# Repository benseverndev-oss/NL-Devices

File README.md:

# NL-Devices

Natural-language → **validated** electronic schematic/netlist + BOM, eventually a
routed PCB exportable to fab (PCBWay/JLCPCB).

An LLM orchestrator composes **pre-verified subcircuit blocks** (not synthesis from
scratch), validated against a ground-truth component database, with deterministic
compile-to-netlist and verification. The product is *correctness*; natural language
is the interface.

## Docs

- **[DESIGN.md](./DESIGN.md)** — product thesis, target architecture, and the
  adopt/build/avoid decisions.
- **[BUSINESS.md](./BUSINESS.md)** — monetization & business-model strategy
  (the layered, sequenced revenue model).
- **[SPIKE.md](./SPIKE.md)** — Phase-0 engineering spike: verified blocks +
  seam validation, and the atopile-vs-SKiDL bake-off. *(Steps 0–6 complete — see
  `spike/`.)*
- **[DECISION.md](./DECISION.md)** — spike decision memo: scorecard + chosen
  substrate/architecture (atopile + custom seam-validator + ngspice harness).
- **[ORCHESTRATOR.md](./ORCHESTRATOR.md)** — NL → validated-design orchestrator
  prototype: composes verified blocks, gated by the seam-validator.
- **[RESEARCH.md](./RESEARCH.md)** — cited prior-art & competitive research with
  confidence levels behind every decision.
- **[GAPS.md](./GAPS.md)** — gap audit: honest distance from the running spike to the
  ultimate goal (verified by executing every component), with prioritized next steps.
- **[SPEC-NL-PLANNER.md](./SPEC-NL-PLANNER.md)** — implementation spec for the top
  gap: wiring a real Claude planner into the existing validator-gated seam, with an
  eval harness and CI.
- **[SPEC-PARTDB.md](./SPEC-PARTDB.md)** — implementation spec for the ground-truth
  part-data layer: a sourced, pinned component snapshot + an offline CI gate that
  catches a wrong LCSC code / MPN / footprint / supply voltage in a block's YAML
  (closes the GAPS §4d 🔴).
- **[SPEC-VALIDATOR-DEPTH.md](./SPEC-VALIDATOR-DEPTH.md)** — deepening the validator
  (3→9 checks, incl. `part-rail-rating` joining it to the part DB, plus
  `power-connectivity` + `i2c-multimaster`) and an adversarial corpus that **measures
  the false-negative rate** (walked 33% → 22% → 0% over the representable known-bad
  designs), with the remaining `NOT_MODELLED` gaps named as the roadmap (GAPS §4c).
- **[SPEC-SPICE.md](./SPEC-SPICE.md)** — replacing the "Ohm's-law-in-a-SPICE-costume"
  electrical gate with an honest analytic dropout check + **genuine ngspice `.tran`
  sims** (I2C rise time, rail droop) that cross-check the analytic limit (GAPS §3/§5.6).
- **[SPEC-FAB-EXPORT.md](./SPEC-FAB-EXPORT.md)** — spiking one fab path: a JLCPCB
  package (real-LCSC BOM + CPL + format-valid Gerber/drill) and a validated **dry-run**
  order, honest that copper routing is still the upstream blocker (GAPS §4e/§5.7).
- **[SPEC-ROUTING.md](./SPEC-ROUTING.md)** — owning the autoroute: a CI-gated pipeline
  (`place.py` + headless **freerouting** + `kicad-cli`) that turns the `ato build` board
  into **routed, DRC-clean copper Gerbers**, folded back into the fab package. Closes the
  GAPS §4e routing 🔴 and reverses the DESIGN §4 autoroute decision (AVOID → qualified BUILD).

> Status: early scoping / pre-build.

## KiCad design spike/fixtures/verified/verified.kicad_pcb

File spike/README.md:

# Spike Log

Progress against the [`SPIKE.md`](../SPIKE.md) plan. Step 0 = toolchain baseline;
Step 1 = the 3-block typed slice in atopile.

---

# Step 0: Toolchain Baseline (COMPLETE ✅)

Green baseline for the [`SPIKE.md`](../SPIKE.md) bake-off. Establishes that both
substrates and the SPICE-validation leg run end-to-end on a trivial circuit, and
records the environment decisions for the real slice (steps 1–6).

## Result — all three legs green

| Leg | Hello-world | Status | Proven capability |
|---|---|---|---|
| **atopile** | `atopile/` divider → `ato build` | ✅ | Compiles, **constraint solver** runs (post-design/post-solve checks), **JLCPCB part-picker resolves real parts**, emits netlist + BOM + `.kicad_pcb` |
| **SKiDL** | `skidl/hello_skidl.py` | ✅ | Builds circuit, **`ERC()` runs** (correctly flagged the open-ended divider nets), emits a KiCad netlist |
| **SPICE** | `skidl/ngspice_check.py` | ✅ | DC operating point via a **BSD-clean ngspice wrapper** (`V(MID)=2.500V`) |

Evidence — atopile picked a real part for the 10 kΩ 0402:
```
Designator,Footprint,Quantity,Value,Manufacturer,Partnumber,LCSC Part #
"R1, R2",R0402,2,10kΩ ±1% 62.5mW,UNI-ROYAL(Uniroyal Elec),0402WGF1002TCE,C25744
```

## Key findings (feed the bake-off + de-risk later steps)

1. **PySpice is dead for our purposes — confirmed empirically.** PySpice 1.5 (the
   last PyPI release, 2021; GitHub "git" is also 1.5) is **incompatible with ngspice
   42**: the shared-lib path errors `Unsupported Ngspice version 42 / Command 'run'
   failed`, and the subprocess path errors `Expected label Circuit instead of Note`
   (its raw parser chokes on ngspice 42's new header). This is exactly the
   maintenance risk flagged in [`RESEARCH.md`](../RESEARCH.md) §4c.
   → **Decision: drive the `ngspice` binary directly** (`ngspice_check.py`).
   ngspice is **BSD** (safe to embed) vs. PySpice's **GPLv3** — so this also keeps
   the SPICE leg out of our proprietary core, as DESIGN.md intended. SKiDL's own
   `skidl.pyspice` mode is therefore unavailable; not needed.

2. **atopile *does* emit a standalone netlist** (`build/builds/divider/divider/divider.net`)
   alongside `.kicad_pcb`, `divider.bom.csv`, and `*.variables.md` / `*.i2c_tree.md`
   reports. → Resolves the open question in SPIKE.md §8.

3. **atopile part-picking needs network** (hits the JLCPCB/LCSC parts DB; ~5 s for
   2 passives). Works under this environment's network policy. Plan for offline/CI.

4. **Substrate API specifics learned** (for writing the real blocks):
   - atopile `Resistor` exposes `unnamed[0]` / `unnamed[1]` (faebryk); `Electrical`
     and `Resistor` must each be `import`ed. Values are native: `10kohm +/- 5%`.
   - SKiDL needs KiCad symbol libs; we use the **monolithic** format (KiCad tag
     `8.0.0`), not GitLab master's new split `*.kicad_symdir/` layout.

5. **Version note:** atopile is **pinned to 0.12.5 on Python 3.13** (latest is 0.15.7,
   but 0.13+ needs Python 3.14, which is RC and crashed the CLI). The pin lives in
   `../scripts/setup.sh` / `setup.ps1`, `../.python-version`, and `atopile/ato.yaml`
   (`>=0.12.5`); `../scripts/check_toolchain.py` keeps them in sync. Upgrade
   deliberately once the 3.14 line stabilizes — newer typed-interface syntax targets 0.14+.

## Reproduce

**Prereqs (Ubuntu 24.04):**
```bash
apt-get install -y ngspice libngspice0-dev        # ngspice 42 (BSD)
# KiCad symbol libs (monolithic 8.0.0 format) for SKiDL:
git clone --depth 1 --branch 8.0.0 \
  https://gitlab.com/kicad/libraries/kicad-symbols.git spike/kicad-symbols
```

**SKiDL + SPICE leg:**
```bash
cd spike/skidl
python3 -m venv .venv && . .venv/bin/activate
pip install -r requirements.txt                   # skidl only (no PySpice)
export KICAD_SYMBOL_DIR=$PWD/../kicad-symbols KICAD8_SYMBOL_DIR=$PWD/../kicad-symbols
python hello_skidl.py        # -> divider.net + ERC
python ngspice_check.py      # -> V(MID)=2.5V  PASS
```

**atopile leg** (pinned atopile 0.12.5 / Python 3.13, via `uv`):
```bash
./scripts/setup.sh                                 # pins + installs ato 0.12.5 / Py 3.13
cd spike/atopile && ato build                      # -> build/builds/divider/...
```
(`scripts/setup.ps1` for Windows. The script wraps `uv python install 3.13` +
`uv tool install atopile==0.12.5 --python 3.13` and verifies the pin.)

## Files (committed)
- `atopile/main.ato`, `atopile/ato.yaml` — the atopile divider + build config
- `skidl/hello_skidl.py` — SKiDL divider + ERC + netlist
- `skidl/ngspice_check.py` — **BSD-clean ngspice op-point primitive** (the SPICE
  leg the validator will reuse)
- `skidl/requirements.txt` — pinned deps (skidl only)

Generated dirs (`build/`, `elec/`, `.venv/`, `kicad-symbols/`) are git-ignored.

---

# Step 1: 3-Block Typed Slice in atopile (COMPLETE ✅, with findings)

`atopile/sensor_node.ato` — the SPIKE.md §2 slice: `5V →[PowerBlock]→ 3V3 →
[McuBlock] + [SensorBlock]`, composed over **typed** seams (`ElectricPower`,
`I2C`), built with `ato build -b sensor_node`.

The three blocks use the faebryk typed-interface library bundled with atopile:
`LDO` (PowerBlock), a custom I2C-controller (`McuBlock`: decoupling + bus
pull-ups), and a real `EEPROM` as the I2C peripheral (`SensorBlock`).

## What works (the moat-relevant wins)

| Capability | Evidence |
|---|---|
| **Typed-interface composition** | 3 blocks connect via `ElectricPower` + `I2C` with a single `~`; build's `post-design` + `post-solve` checks pass |
| **Constraint solver validates invariants** | `assert power_out.voltage within 3.3V +/- 5%` etc. solve; LDO `output_voltage` resolved to **`[3.234V, 3.366V]`** (= 3.3V ±2%) in the variable report |
| **Passive part-picking → real parts** | BOM picks real LCSC parts: `100nF C14663`, `1µF C52923`, `10µF C19702`, `4.7kΩ ×2 C25900` |
| **Typed seams appear in the netlist** | `sensor_node.net` (243 lines) carries real nets `SCL`, `SDA`, `power-VCC`, `power_in-VCC`, `GND` |
| **Standalone artifacts** | netlist + `sensor_node.bom.csv` + `*.variables.md` + `*.kicad_pcb` |

## Findings / limits (what this teaches us about the block library)

1. **IC part-picking is NOT automatic.** The generic `LDO` and `EEPROM` produced
   `WARNING: No pickers and no footprint` and are **absent from the BOM** — only
   passives auto-resolve. This confirms the RESEARCH.md flag (IC picker coverage
   = Low). *Net: a "verified block" with a real IC is real work, not a free pick.*
2. **Pinning a concrete IC requires a component *definition*.** Setting
   `regulator.lcsc_id = "C6186"` on a generic instance is rejected:
   *"You can't assign to a `component` with a specific part number outside of its
   definition."* → concrete parts must be authored as component blocks (or via
   `ato create part`, which fetches the footprint/pinmap). **This is precisely the
   per-block effort our library must own** — and it's where the datasheet/part-data
   moat (RESEARCH.md §3) actually bites.
3. **`i2c-tree` report is empty** — atopile's I2C semantic report needs concrete,
   address-bearing devices (the EEPROM didn't resolve to a part). Address/bus-rule
   checking therefore depends on real IC bindings, not just the typed interface.

## Implication for the bake-off

atopile delivers the **typed seams + constraint solving + passive resolution** for
free — a real head start on the seam-validation moat. The gap is **concrete IC
binding** (footprints, pinmaps, addresses), which is unavoidable block-library work
in *any* substrate. Step 3 will test whether atopile's typed checks catch the
injected seam faults, or whether we still need a custom seam layer.

## Reproduce
```bash
cd spike/atopile && ato build -b sensor_node    # atopile 0.12.5, Python 3.13
# artifacts in build/builds/sensor_node/
```

---

# Step 2: Same Slice in SKiDL (COMPLETE ✅) + the bake-off contrast

`skidl/sensor_node_skidl.py` — the identical slice as three `@subcircuit`
functions (`power_block` AMS1117-3.3, `mcu_block` I2C controller, `sensor_block`
24LC256 EEPROM), composed over shared nets, with `ERC()` + `generate_netlist()`.

## What works
| Capability | Evidence |
|---|---|
| **Real ICs in the netlist** | `sensor_node.net` (451 lines) contains **`AMS1117-3.3`** and **`24LC256`** as real components + full passive BOM — by naming the KiCad symbol directly (no picker needed) |
| **Pin-level ERC (controllable)** | first run flagged *"Insufficient drive current on net 5V/GND for POWER-IN pin"* (correct!); adding `net.drive = POWER` (≈ KiCad PWR_FLAG) → **"No errors or warnings"** |
| **Hierarchy preserved** | netlist carries `/power_block1/`, `/mcu_block1/`, `/sensor_block1/` sheets |
| **Seam nets** | `5V`, `3V3`, `GND`, `SCL`, `SDA` |

## The bake-off contrast (the core decision input)

| Dimension | atopile (step 1) | SKiDL (step 2) |
|---|---|---|
| **Typed port contract** (voltage domain, I2C) | ✅ native (`ElectricPower`/`I2C`) | ❌ bare nets — *we'd build the type layer* |
| **Constraint solving** (params + tolerance) | ✅ LDO out solved `[3.234V, 3.366V]` | ❌ none |
| **Pin-level ERC** | ⚠️ post-design checks (not classic pin ERC) | ✅ real, type-aware, controllable |
| **IC part resolution** | ❌ LDO/EEPROM **don't auto-pick** | ✅ name the symbol → IC in netlist |
| **Passive resolution** | ✅ auto-picked to **real LCSC MPNs** | ⚠️ manual (you give value + footprint) |
| **Manufacturing data (BOM w/ MPN)** | ✅ LCSC ids | ❌ generic KiCad symbols, no MPN |
| **SPICE** | ❌ none | ✅ via our direct-ngspice wrapper |

**Conclusion — the two are complementary, exactly as hypothesized.** atopile owns
the *typed seam + constraint solving + manufacturable passives* (the moat-relevant
authoring layer); SKiDL/KiCad owns *real IC definitions + pin-level ERC + SPICE*
(the electrical-validation layer). Neither alone is a complete substrate. The
**deciding test is Step 3**: does atopile's typed model actually *catch* the
injected seam faults? If yes, atopile-as-author + a SKiDL/ngspice validation
harness is the hybrid; if no, we build a custom seam layer regardless.

## Reproduce
```bash
cd spike/skidl && . .venv/bin/activate
export KICAD_SYMBOL_DIR=$PWD/../kicad-symbols KICAD8_SYMBOL_DIR=$PWD/../kicad-symbols
python sensor_node_skidl.py        # -> ERC clean + sensor_node.net
```

---

# Step 3+4: Seam-fault detection — THE MOAT MEASUREMENT (COMPLETE ✅)

The decisive test: inject the three SPIKE.md §4 seam faults and measure how many
atopile catches **natively** vs. how many we must build. Then prove our own
seam-validator catches all three.

## Part A — what atopile catches for free

Each fault is a build target in `atopile/sensor_node.ato` (modules
`AppFault1PowerDomain`, `AppFault2NoPulls`, `AppFault3AddrCollision`). Consumer
blocks declare their rail invariant (`assert power.voltage within 3.3V +/- 5%`).

| Fault | atopile native result | Caught? |
|---|---|---|
| **1. Power-domain mismatch** (MCU on 5V) | build **fails**: `Contradiction: Intersection of literals is empty — power5v.voltage [5V±5%] vs mcu.power.voltage [3.135V,3.465V]` | ✅ **YES** (constraint solver) |
| **2. Missing I2C pull-ups** | build **succeeds** — `requires_pulls` trait exists but is not enforced | ❌ no |
| **3. I2C address collision** (two peripherals @ 0x50) | build **succeeds** — address rules need concrete addressed devices | ❌ no |

**Finding:** atopile's typed model + constraint solver gives the **hardest** seam
check — parametric power-domain compatibility — *for free*. The I2C **topology**
rules (pull-ups, addresses) it does **not** enforce. So the seam-validation moat is
real but **partially pre-built by atopile** (the parametric third, the expensive one).

## Part B — our seam-validator catches all three

`seam_validator.py` (~150 lines, no deps, substrate-independent) runs over a typed
block-graph — the "verified block" contract from SPIKE.md §3 — and checks all three
seams. Output:

```
design                   power  pulls  addr   verdict
--------------------------------------------------------
correct                  ok     ok     ok      PASS
fault1_power_domain      FAIL   ok     ok      PASS
    └─ POWER: rail '5V' = [4.750V,5.250V] is outside 'mcu' accepted [3.135V,3.465V]
fault2_no_pullups        ok     FAIL   ok      PASS
    └─ I2C: bus 'i2c_bus' has no pull-up provider (SCL/SDA float)
fault3_addr_collision    ok     ok     FAIL    PASS
    └─ I2C: bus 'i2c_bus' address 0x50 collision ('sensor' and 'sensor_b')
--------------------------------------------------------
RESULT: PASS — validator caught exactly the injected faults
```

Each fault triggers **exactly** its intended check (no false positives) and the
correct design passes — SPIKE.md **acceptance criterion #3 met**.

## Verdict on the thesis (Risk #1)

**The seam-validation moat is real and cheap to build.** All three seam rules are
small, deterministic, and explainable; atopile already pre-builds the hardest
(parametric power domains) via its constraint solver. This is strong evidence for
the architecture: **atopile-as-author (typed seams + constraint solving) + a thin
custom seam-validator (I2C/topology rules) + the SKiDL/ngspice harness for
electrical sanity.** The expensive part is *not* the validator — it's the
verified-block library / IC part data (the Step-1 finding), which is where effort
should go.

## Reproduce
```bash
cd spike && python3 seam_validator.py                       # all 3 faults caught
cd atopile && ato build -b fault1   # atopile catches this (build fails by design)
                ato build -b fault2  # builds clean -> atopile misses (our checker catches)
                ato build -b fault3  # builds clean -> atopile misses (our checker catches)
```

---

# Next: First REAL verified IC blocks (the first moat brick) ✅

Per [`DECISION.md`](../DECISION.md), effort belongs in the verified-block / IC
part-data library. `atopile/verified_slice.ato` authors the first real ones.

## Pattern: atomic part + typed wrapper = a verified block

`ato create part --search <LCSC-id> --accept-single` fetches a real part (footprint,
symbol, pinmap, 3D model, `has_part_picked` MPN) as an **atomic component with bare
`signal` pins**. A *verified block* wraps that atomic part in a **typed module**
(`ElectricPower`/`I2C`) with **invariants** — so it is both **manufacturable** (real
MPN) and **seam-checkable** (typed ports). Two authored so far, in
`elec/src/parts/`:

| Block | Real part | LCSC | Footprint |
|---|---|---|---|
| `PowerBlock` | AMS1117-3.3 LDO | **C6186** | SOT-223-3 |
| `SensorBlock` | AT24C256C I2C EEPROM | **C6482** | SOIC-8 |

## Result: a fully manufacturable BOM (every line a real MPN)
```
Designator,Footprint,Quantity,Value,Manufacturer,Partnumber,LCSC Part #
C1,C0402,1,1µF…,Samsung,CL05A105KA5NQNC,C52923
C2,C0603,1,10µF…,Samsung,CL10A106KP8NNNC,C19702
C3,C0603,1,100nF…,YAGEO,CC0603KRX7R9BB104,C14663
"R1, R2",R0402,2,4.7kΩ…,UNI-ROYAL,0402WGF4701TCE,C25900
U1,SOT-223-3,1,,Advanced Monolithic Systems,AMS1117-3.3,C6186
U2,SOIC-8,1,,Microchip Tech,AT24C256C-SSHL-T,C6482
```
This closes the Step-1 gap (ICs absent from the BOM): with authored blocks, **both
ICs resolve with real MPNs**.

## Finding → a contract requirement
The **i2c-tree is still empty** even with a real addressed EEPROM: atopile can't
infer the I2C address from grounded A0/A1/A2 pins. So **the verified-block contract
must carry the I2C address as explicit metadata** (not inferred) — which is exactly
what `seam_validator.py` already consumes for the address-collision check. The
authored atomic part gives manufacturability; **our block contract supplies the
semantic metadata (address, supply range) the seam checks need.**

## Reproduce
```bash
cd spike/atopile
ato create part --search C6186 --accept-single   # LDO
ato create part --search C6482 --accept-single   # EEPROM
ato build -b verified                            # BOM has U1 C6186 + U2 C6482
```

---

# Block-contract schema + contract-driven validation ✅

Formalizes the verified-block contract (SPIKE.md §3) and wires the seam-validator
to read **authored blocks**, not hand-built Python. Three pieces:

- **`blocks/*.yaml`** — the verified-block contracts. Each carries: `id`/`version`/
  `function`, a `bound_part` (real LCSC MPN + footprint), typed `ports`, and
  `invariants`. The **semantic metadata atopile cannot infer lives here** — I2C
  `address`, supply `voltage`/`tolerance`.
- **`slices/*.yaml`** — a composition: block `instances` + `rails` + `buses`
  (wiring typed ports into seams).
- **`block_contract.py`** — loads + **schema-validates** the blocks, composes the
  slice into a `seam_validator.Design`, and runs the three seam checks.

## The schema is enforced
`block_contract.py` rejects malformed blocks loudly — e.g. a peripheral missing its
address:
```
ValueError: bad.yaml: i2c peripheral 'i2c' missing 'address'
            (required — atopile cannot infer it)
```
That rule encodes the Step-3/verified-block finding directly into the contract.

## It works end-to-end
```
$ python3 block_contract.py --faults
loaded 3 verified blocks: mcu_i2c_controller, power_3v3_ldo, sensor_eeprom_24c256
  · power_3v3_ldo            part=C6186
  · sensor_eeprom_24c256     part=C6482
validating authored slice:
  [PASS] sensor_node
injecting seam faults (each must be caught):
  [caught] fault: MCU on 5V rail        └─ POWER: rail '5V' [4.750V,5.250V] outside 'mcu' [3.135V,3.465V]
  [caught] fault: no I2C pull-ups       └─ I2C: bus 'i2c_bus' has no pull-up provider
  [caught] fault: duplicate I2C address └─ I2C: bus 'i2c_bus' address 0x50 collision ('sensor','sensor_b')
RESULT: PASS
```

**Significance:** the validator now consumes the **authored block library** — the
same typed, manufacturable blocks (`C6186`, `C6482`) that build in atopile. This is
the library format the LLM orchestrator will emit/target: parts give
manufacturability, the contract gives the seam-checkable semantics. (Needs `pyyaml`,
preinstalled with system `python3` here.)

## Reproduce
```bash
cd spike && python3 block_contract.py --faults
```

---

# Orchestrator + codegen — NL → manufacturable BOM (loop closed) ✅

`orchestrator.py` composes verified blocks from a NL spec; the **gate** runs
topology (`seam_validator`) + I2C **auto-addressing/capacity** + an **electrical**
stage (`electrical.py`, ngspice rail-load & pull-up current); `codegen.py` emits a
top-level `App.ato` over the authored modules in `atopile/verified_lib.ato` and
`ato build`s it.

```
$ python3 orchestrator.py --build
SPEC: A microcontroller that logs temperature readings to memory over I2C
   -> VALIDATION: PASS   -> CODEGEN+BUILD: manufacturable BOM
        U1 AMS1117-3.3 C6186 · U2 LM75 C477979 (0x48) · U3 AT24C256 C6482 (0x50)
SPEC: An MCU with three EEPROM memory chips on one I2C bus
   -> VALIDATION: PASS   (auto-addressed 0x50/0x51/0x52) -> 3x C6482 in BOM
SPEC: An MCU with nine EEPROM memory chips on one I2C bus
   -> VALIDATION: REJECTED   └─ address space exhausted (0x50..0x57 full)
```

**NL → orderable board, gated by validation.** See [`../ORCHESTRATOR.md`](../ORCHESTRATOR.md).
`python3 electrical.py` shows the electrical gate rejecting an overloaded rail and a
too-small pull-up.

## Reproduce
```bash
cd spike && python3 orchestrator.py --build    # NL -> compose -> gate -> BOM
```

---

# Real MCU block — the board gets a brain (GAPS #2) ✅

The `mcu_i2c_controller` block was a placeholder (`bound_part: null` — just a
decoupling cap + two pull-ups), so the "sensor node" had no processor and wouldn't
function. It is now a **real STM32F103C8T6** (ARM Cortex-M3, LQFP-48, LCSC `C8734`,
214k in stock), authored via `ato create part --search C8734` and wrapped as a typed
`McuBlock` in [`atopile/verified_lib.ato`](./atopile/verified_lib.ato):

- **Power:** all three VDD pins + VBAT + VDDA to the 3V3 rail; all VSS + VSSA to GND.
- **Decoupling:** 100nF per VDD pin + a 4.7µF bulk + a 1µF on VDDA.
- **Reset:** NRST pull-up (10k) + 100nF to GND (standard RC).
- **Boot:** BOOT0 → GND via 10k (boot from main flash).
- **I2C1** on PB6 (SCL) / PB7 (SDA) onto the typed bus, owning the 4.7k bus pull-ups.
- Runs on the internal 8 MHz RC oscillator — **no crystal needed to function**; SWD
  (PA13/PA14) is left for a board-level programming header.

## Result: the temperature-logger BOM now includes the MCU
```
U1, LQFP-48,    STM32F103C8T6,    C8734     (MCU — the brain)
U2, SOT-223-3,  AMS1117-3.3,      C6186     (LDO)
U3, SOIC-8,     LM75AIMX/NOPB,    C477979   (temp sensor @0x48)
U4, SOIC-8,     AT24C256C-SSHL-T, C6482     (EEPROM @0x50)
+ decoupling (4×100nF, 4.7µF, 2×1µF), NRST RC, BOOT0 10k, I2C pull-ups — all real MPNs
```
Closes GAPS #2: the verified-block pattern is proven past passives + small ICs to a
**48-pin microcontroller**, and `orchestrator.py` now reports `mcu = mcu_i2c_controller
[C8734]` (was `[abstract]`). The contract in
[`blocks/mcu_i2c_controller.yaml`](./blocks) carries the real MPN + worst-case 50mA
run current (which the electrical gate uses for rail loading).

## Reproduce
```bash
cd spike/atopile && ato create part --search C8734 --accept-single   # fetch the MCU
cd spike && python3 orchestrator.py --build                          # MCU resolves in the BOM
```

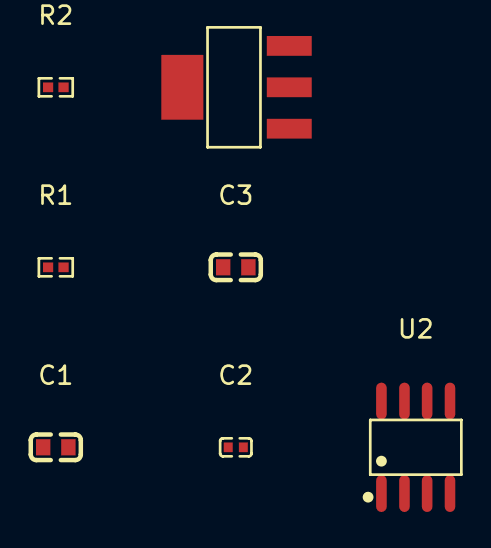
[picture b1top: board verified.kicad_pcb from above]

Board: 2 copper layers, 7 parts (0 on the bottom side), 5 nets, no tracks yet.

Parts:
C1: 100nF ±10% 50V X7R; C0603
C2: 1µF ±10% 25V X5R; C0402
C3: 10µF ±10% 10V X5R; C0603
R1, R2: 4.7kΩ ±1% 62.5mW; R0402
U1: SOT-223-3_L6.5-W3.4-P2.30-LS7.0-BR
U2: SOIC-8_L4.9-W3.9-P1.27-LS6.0-BL

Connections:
GND: C1.2, C2.2, C3.2, U1.1, U2.1, U2.2, U2.3, U2.4, U2.7
SCL: R1.1, U2.6
SDA: R2.1, U2.5
power-VCC: C1.1, C3.1, R1.2, R2.2, U1.2, U1.4, U2.8
power_in-VCC: C2.1, U1.3

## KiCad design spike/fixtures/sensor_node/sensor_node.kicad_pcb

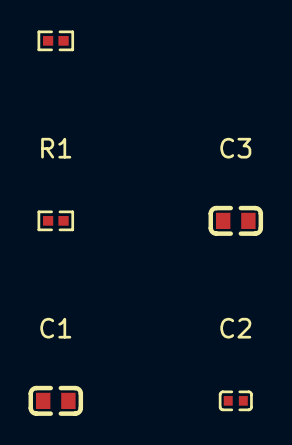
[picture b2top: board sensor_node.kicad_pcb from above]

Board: 2 copper layers, 5 parts (0 on the bottom side), 2 nets, no tracks yet.

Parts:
C1: 100nF ±10% 50V X7R; C0603
C2: 1µF ±10% 25V X5R; C0402
C3: 10µF ±10% 10V X5R; C0603
R1, R2: 4.7kΩ ±1% 62.5mW; R0402

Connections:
GND: C1.2, C2.2, C3.2
power-VCC: C1.1, C3.1, R1.2, R2.2

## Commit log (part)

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2026-06-08 Add competitive research and design/strategy docs
    Capture the prior-art landscape (circuits-as-code DSLs, AI-EDA copilots,
    component-data licensing, research SOTA, market/moat) and the resulting
    adopt/build/avoid decisions for the NL -> validated schematic + BOM wedge.
    - RESEARCH.md: cited findings with confidence levels and flagged unverified items
    - DESIGN.md: revised thesis, target architecture, decisions, and risks
    - README: project summary and doc links
2026-06-08 Add monetization & business-model strategy
    Push on the monetization risk (Risk #2): the per-seat trap, two reframes
    (payer != user; price the avoided respin), five model options scored against
    fab-economics and supplier-pays research, and a layered/sequenced revenue
    model with open unknowns to validate.
    - BUSINESS.md: the monetization brief
    - DESIGN.md: link Risk #2 to the brief
2026-06-08 Add Phase-0 spike scope: verified blocks + seam validation
    Scope the vertical-slice spike that de-risks the moat: a regulated-rail + I2C
    sensor slice expressed as 3 verified blocks with typed port contracts, an
    atopile-vs-SKiDL bake-off scorecard, injected seam faults the validator must
    catch, acceptance criteria, and a 1-2 week plan.
    - SPIKE.md: the spike scope
    - DESIGN.md / README: link the spike
2026-06-09 Spike step 0: green toolchain baseline (atopile, SKiDL, ngspice)
    Stand up the substrates and SPICE leg; reproduce a hello-world divider on each.
    - atopile 0.12.5: builds, constraint solver runs, JLCPCB part-picker resolves a
    real LCSC part (C25744), emits netlist + BOM + kicad_pcb
    - SKiDL 2.2.3: builds circuit, ERC runs, emits KiCad netlist (KiCad 8.0.0 symbols)
    - SPICE: PySpice 1.5 confirmed incompatible with ngspice 42; replaced with a
    BSD-clean direct-ngspice op-point wrapper (keeps SPICE out of the GPL surface)
2026-06-09 Spike step 1: 3-block typed slice in atopile
    Compose PowerBlock(LDO) + McuBlock(I2C controller) + SensorBlock(EEPROM) over
    typed ElectricPower + I2C seams; builds to netlist + BOM with the constraint
    solver validating rail-voltage invariants (LDO out solved to 3.234-3.366V).
    Findings: typed composition + constraint solving + passive part-picking work
    for free, but IC binding (LDO/EEPROM) is not automatic - concrete parts need a
    component definition, which is the per-block work our verified-block library
2026-06-09 Spike step 2: same 3-block slice in SKiDL + bake-off contrast
    Mirror the slice as three @subcircuit blocks (AMS1117-3.3, I2C controller,
    24LC256 EEPROM); ERC clean after power-drive flags; netlist carries real ICs
    and the @subcircuit hierarchy.
    Bake-off crystallizes the tools as complementary: atopile owns typed seams +
    constraint solving + manufacturable passives but cannot auto-pick ICs; SKiDL
    owns real IC definitions + pin-level ERC + SPICE but has no typed seam contract.
2026-06-09 Spike step 3+4: seam-fault detection (the moat measurement)
    Inject the three SPIKE.md seam faults and measure native vs. built detection.
    Native atopile probe (fault modules in sensor_node.ato):
    - Fault 1 power-domain mismatch: CAUGHT (constraint solver contradiction)
    - Fault 2 missing I2C pull-ups: NOT caught (requires_pulls not enforced)
    - Fault 3 I2C address collision: NOT caught
    Our seam_validator.py (~150 lines, deterministic, substrate-independent) catches
2026-06-09 Spike step 5+6: rail SPICE check + decision memo (spike complete)
    Step 5: ngspice DC op-point on slice-relevant seams - 3V3 rail under load =
    3.295V (in tolerance), I2C pull-up sink = 0.701mA (within spec).
    Step 6: filled scorecard and DECISION.md. Decision: hybrid with atopile as the
    authoring substrate (typed seams + constraint solver + manufacturable passives,
    weighted 63 vs SKiDL 51), our substrate-independent seam-validator for I2C/
    topology rules, ngspice (BSD) harness for SPICE, SKiDL/KiCad as IC-definition
2026-06-09 Author first real verified IC blocks (LDO + EEPROM) — the moat brick
    Use 'ato create part' to fetch real LCSC parts and wrap them in typed blocks:
    - PowerBlock: AMS1117-3.3 LDO (C6186), typed ElectricPower ports
    - SensorBlock: AT24C256C I2C EEPROM (C6482), typed I2C + power ports
    The verified slice now produces a FULLY manufacturable BOM - both ICs (U1 C6186,
    U2 C6482) plus passives, every line a real LCSC MPN - closing the step-1 gap.
    Finding: atopile won't infer the I2C address from grounded pins (i2c-tree stays
2026-06-09 Formalize block-contract schema + wire validator to authored blocks
    Add the verified-block contract format and close the loop from authored library
    to seam validation:
    - blocks/*.yaml: verified-block contracts (id, version, bound LCSC part, typed
    ports, invariants). Semantic metadata atopile can't infer (I2C address, supply
    range) lives in the contract.
    - slices/sensor_node.yaml: declarative composition (instances + rails + buses).
2026-06-09 Start NL->validated-design orchestrator prototype
    Close the core loop: NL spec -> compose verified blocks -> seam-validator gate.
    - orchestrator.py: pluggable Planner; HeuristicPlanner composes blocks from the
    catalog by capability keywords; LLMPlanner is the seam (emit_plan tool with
    block_id ENUM-constrained to catalog ids -> can't invent parts; accepts
    validator feedback for retry). Pipeline gates every design.
    - Demos: 'temperature logger' and 'two EEPROMs' PASS with real parts (C6186/
2026-06-09 Close the loop: slice -> .ato codegen -> manufacturable BOM
    Add codegen from an orchestrator slice to atopile, ending the NL->design loop
    in a real BOM:
    - verified_lib.ato: authored verified-block MODULES (real parts: AMS1117 C6186,
    AT24C256 x2 @0x50/0x51 C6482, LM75 C477979) wrapping atomic parts in typed
    interfaces with address strapping.
    - codegen.py: emits the top-level App from a slice (instances + rails + buses),
2026-06-09 Add gap audit: distance from running spike to the ultimate goal
    Audits the four goal pillars (NL interface, verified-block library,
    validation engine, ground-truth part DB) plus the layout->fab tail and
    business risks. Every spike component was executed, not just read, so the
    audit distinguishes what runs from what the docs claim:
    - NL leg is a keyword router; the LLM has never planned (call_model=None,
    run() never loops on feedback).
2026-06-09 Spec the top gap: make the NL planner real
    Implementation spec for GAPS #1 — turning the project's namesake from a
    keyword router into a real, validator-gated Claude planner. Scoped narrow
    because the seam already exists in orchestrator.py (LLMPlanner, the
    enum-constrained emit_plan tool, the call_model contract).
    Covers: an Anthropic call_model (claude-opus-4-8, forced emit_plan tool,
    enum-constrained block_ids); fixing run() to implement the feedback->retry
2026-06-09 Implement gap #1: wire a real NL planner + feedback loop + eval + CI
    Implements SPEC-NL-PLANNER.md, turning the project's namesake from a
    keyword router into a real, validator-gated LLM planner.
    - spike/llm_client.py: Anthropic call_model (claude-opus-4-8) forcing the
    enum-constrained emit_plan tool — the model can only select catalog blocks.
    - orchestrator.py: run() now implements the actual feedback->retry loop
    (previously an unused 'feedback' param the docs wrongly called 'wired').
2026-06-09 Author a real MCU block (GAPS #2): STM32F103C8T6
    Replaces the placeholder mcu_i2c_controller (bound_part: null — just a cap
    and two pull-ups, no processor) with a real STM32F103C8T6 ARM Cortex-M3
    (LQFP-48, LCSC C8734), fetched via 'ato create part' and wrapped as a typed
    McuBlock in verified_lib.ato with full support circuitry:
    - all VDD/VBAT/VDDA -> 3V3, all VSS/VSSA -> GND
    - decoupling: 100nF per VDD pin + 4.7uF bulk + 1uF on VDDA
2026-06-09 Stand up route CI job skeleton + toolchain pins (plan Task 1)
2026-06-09 route job: probe pcbnew via system python, never red-fail the PROBE step
2026-06-09 Re-capture verified board fixture (LDO+EEPROM+I2C) [skip ci]
2026-06-09 Close the last two validator false negatives (power-connectivity, i2c-multimaster)
    The validator corpus published two remaining representable false negatives
    (GAPS §4c). Build both as real checks, following the part-rail-rating pattern:
    - power-connectivity: every active (I2C) device must be a sink on some rail;
    an orphan device wired to no rail floated past every other check, which only
    reason about the rails a block IS on.
    - i2c-multimaster: two controllers on one bus need arbitration that simple
2026-06-10 Wire the STM32 into a build target: verified_mcu (real MCU + LDO + EEPROM)
    Decision 0004's deferred follow-up. The real STM32F103C8T6 McuBlock already
    lived in verified_lib.ato (power/decoupling/reset/BOOT0/I2C1 on PB6/PB7) but was
    never composed into an App or a build target, so the only routed board (verified)
    had no silicon. This adds verified_mcu.ato:App composing PowerBlock (AMS1117-3.3,
    C6186) + the real McuBlock (STM32F103C8T6, C8734) + SensorBlock (AT24C256, C6482),
    and registers a 'verified_mcu' build.
2026-06-10 Route the verified_mcu board through the autoroute gate
    Add the STM32 board (verified_mcu: 48-pin LQFP + LDO + EEPROM) to the CI route
    job as a second hard-gated invocation. The route pipeline is board-agnostic
    (--board / --work), and the deterministic grid placement scales with footprint
    count, so no code change is needed — just the new step against
    elec/layout/verified_mcu/verified_mcu.kicad_pcb (path confirmed from the build
    step; 12/12 parts picked). The STM32 (C8734) is in the snapshot, so the routed
2026-06-10 Defer verified_mcu autoroute; record the two blockers (restore green CI)
    An autoroute attempt on the 48-pin STM32 board (CI run #48) failed the hard gate
    with a precise, honest diagnosis:
    - unrouted=13/42: freerouting places 0 vias, so it can't complete a dense
    2-layer route — needs via-padstack support in the Specctra DSN export.
    - drc_violations=29: all solder_mask_bridge on the LQFP-48 0.5mm-pitch pads —
    a fine-pitch mask-policy question, orthogonal to routing.
2026-06-10 Routing iter 1: relax in-footprint mask bridges + DSN via diagnostic
    Toward routing verified_mcu (the 48-pin STM32 board). Two blockers from run #48:
    1. solder_mask_bridge (29): place.allow_mask_bridges() flips the board's
    (allow_soldermask_bridges_in_footprints) switch to yes — KiCad's own per-board
    control for fine-pitch footprints (the LQFP-48 0.5mm pads), a fab-capability
    matter not a defect. Only in-footprint bridges are relaxed; route/copper
    clearances keep their teeth. Offline-tested in place.py --selftest.
2026-06-10 Defer verified_mcu autoroute (placement-engine problem); restore green CI
    Two routing iterations (CI #50/#51) produced a definitive diagnosis:
    - Vias: SOLVED — DSN defines Via[0-1]_600:300_um and freerouting uses it.
    - Real blocker is PLACEMENT: the naive grid scatters passives from the 48-pin
    MCU and the large GND/3V3 multi-pad nets are routed point-to-point with no
    copper pour, so freerouting thrashes (999 passes, ~82 GB RAM, >=8 nets
    unrouted, non-deterministic). Needs net-aware placement + ground/power planes.
2026-06-10 Routing iter 3: block-cluster placement + mask-bridge DRC exclusion + bound freerouting
    Toward routing verified_mcu (the 48-pin STM32 board), on a dedicated branch so
    PR #10 stays green.
    - place.py: cluster placement by atopile block. Footprints carry
    (property "atopile_address" "mcu.cap"); group each block's parts contiguously,
    IC-anchor first, so the grid drops decoupling caps / pull-ups next to their IC and
    intra-block nets (power/decoupling/bus) stay short. Offline-tested (block parse +
2026-06-10 verified_mcu now routes 0/0: mark done, drop redundant diagnostic
    Routing iter 3 (CI #54) passed the hard gate: verified_mcu routes unrouted=0,
    drc_violations=0, freerouting converged in 6 passes / 1.6 GB (vs the prior
    ~1000-pass / 82 GB runaway). Block-cluster placement was sufficient — no GND/3V3
    pours needed at this size.
    - GAPS §4e: mark the STM32 board as BUILDS *and* ROUTES (decision 0004 closed).
    - ci.yml: drop the now-redundant route diagnostic (the == GATE == line reports
2026-06-10 Route the STM32 board (verified_mcu) → 0-unrouted / 0-DRC copper (#13)
2026-06-10 Create + ingest W25Q128 (C97521) SPI flash part [skip ci]
